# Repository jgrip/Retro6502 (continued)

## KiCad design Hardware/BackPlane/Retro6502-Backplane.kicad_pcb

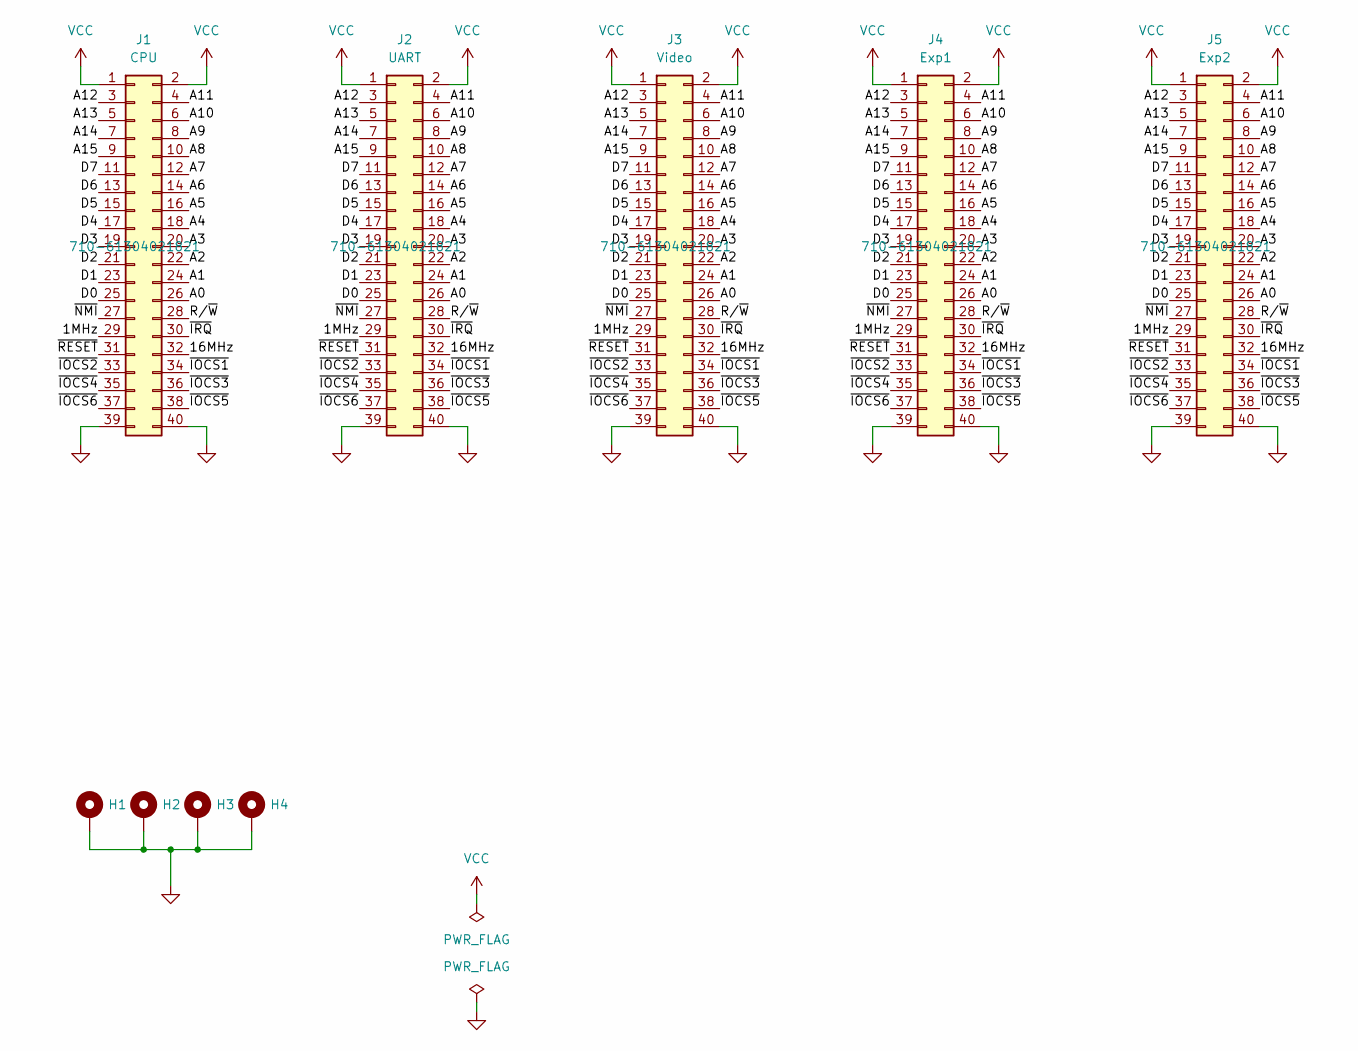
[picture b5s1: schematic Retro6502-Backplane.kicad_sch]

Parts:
H1, H2, H3, H4: MountingHole_Pad; MountingHole_3.2mm_M3_Pad_Via
J1: CPU; PinSocket_2x20_P2.54mm_Vertical; Mouser 710-61304021821
J2: UART; PinSocket_2x20_P2.54mm_Vertical; Mouser 710-61304021821
J3: Video; PinSocket_2x20_P2.54mm_Vertical; Mouser 710-61304021821
J4: Exp1; PinSocket_2x20_P2.54mm_Vertical; Mouser 710-61304021821
J5: Exp2; PinSocket_2x20_P2.54mm_Vertical; Mouser 710-61304021821

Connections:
/1MHz: J1.29, J2.29, J3.29, J4.29, J5.29
/16MHz: J1.32, J2.32, J3.32, J4.32, J5.32
/A0: J1.26, J2.26, J3.26, J4.26, J5.26
/A1: J1.24, J2.24, J3.24, J4.24, J5.24
/A2: J1.22, J2.22, J3.22, J4.22, J5.22
/A3: J1.20, J2.20, J3.20, J4.20, J5.20
/A4: J1.18, J2.18, J3.18, J4.18, J5.18
/A5: J1.16, J2.16, J3.16, J4.16, J5.16
/A6: J1.14, J2.14, J3.14, J4.14, J5.14
/A7: J1.12, J2.12, J3.12, J4.12, J5.12
/A8: J1.10, J2.10, J3.10, J4.10, J5.10
/A9: J1.8, J2.8, J3.8, J4.8, J5.8
/A10: J1.6, J2.6, J3.6, J4.6, J5.6
/A11: J1.4, J2.4, J3.4, J4.4, J5.4
/A12: J1.3, J2.3, J3.3, J4.3, J5.3
/A13: J1.5, J2.5, J3.5, J4.5, J5.5
/A14: J1.7, J2.7, J3.7, J4.7, J5.7
/A15: J1.9, J2.9, J3.9, J4.9, J5.9
/D0: J1.25, J2.25, J3.25, J4.25, J5.25
/D1: J1.23, J2.23, J3.23, J4.23, J5.23
/D2: J1.21, J2.21, J3.21, J4.21, J5.21
/D3: J1.19, J2.19, J3.19, J4.19, J5.19
/D4: J1.17, J2.17, J3.17, J4.17, J5.17
/D5: J1.15, J2.15, J3.15, J4.15, J5.15
/D6: J1.13, J2.13, J3.13, J4.13, J5.13
/D7: J1.11, J2.11, J3.11, J4.11, J5.11
/R/~W: J1.28, J2.28, J3.28, J4.28, J5.28
/~IOCS1: J1.34, J2.34, J3.34, J4.34, J5.34
/~IOCS2: J1.33, J2.33, J3.33, J4.33, J5.33
/~IOCS3: J1.36, J2.36, J3.36, J4.36, J5.36
/~IOCS4: J1.35, J2.35, J3.35, J4.35, J5.35
/~IOCS5: J1.38, J2.38, J3.38, J4.38, J5.38
/~IOCS6: J1.37, J2.37, J3.37, J4.37, J5.37
/~IRQ: J1.30, J2.30, J3.30, J4.30, J5.30
/~NMI: J1.27, J2.27, J3.27, J4.27, J5.27
/~RESET: J1.31, J2.31, J3.31, J4.31, J5.31
GND: H1.1, H2.1, H3.1, H4.1, J1.39, J1.40, J2.39, J2.40, J3.39, J3.40, J4.39, J4.40, J5.39, J5.40
VCC: J1.1, J1.2, J2.1, J2.2, J3.1, J3.2, J4.1, J4.2, J5.1, J5.2

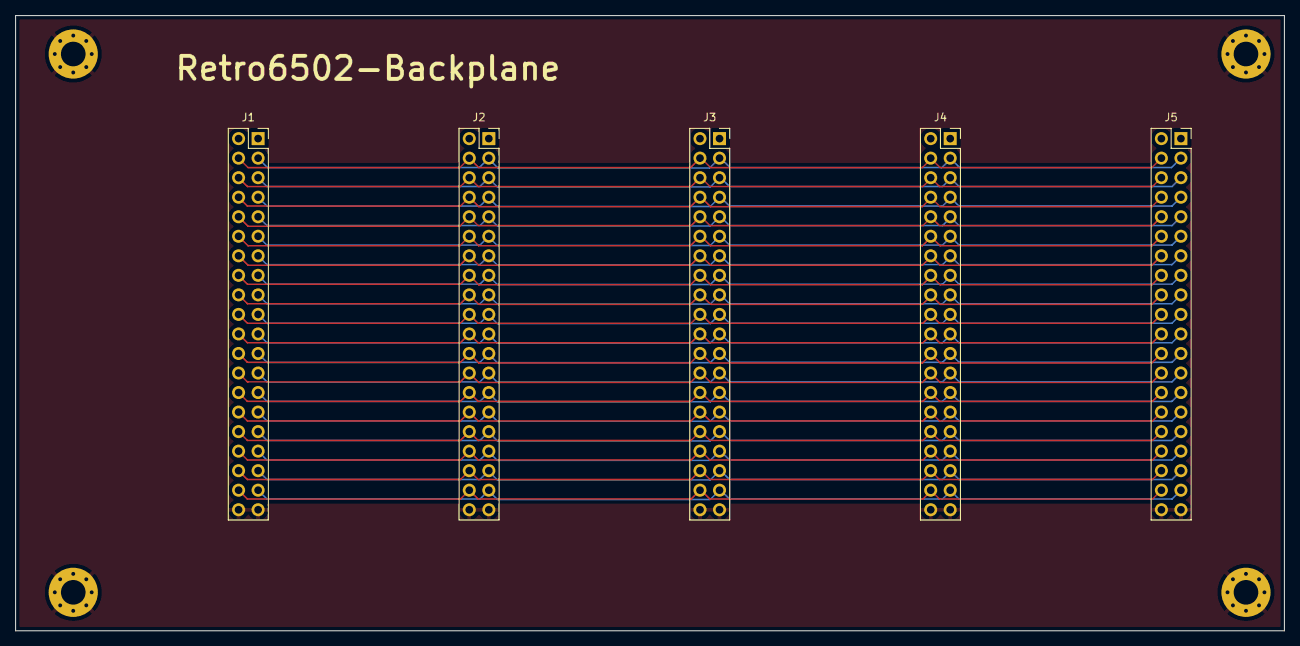
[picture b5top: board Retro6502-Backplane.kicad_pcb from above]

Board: 2 copper layers, 165.0 x 80.0 mm, 9 parts (0 on the bottom side), 38 nets.

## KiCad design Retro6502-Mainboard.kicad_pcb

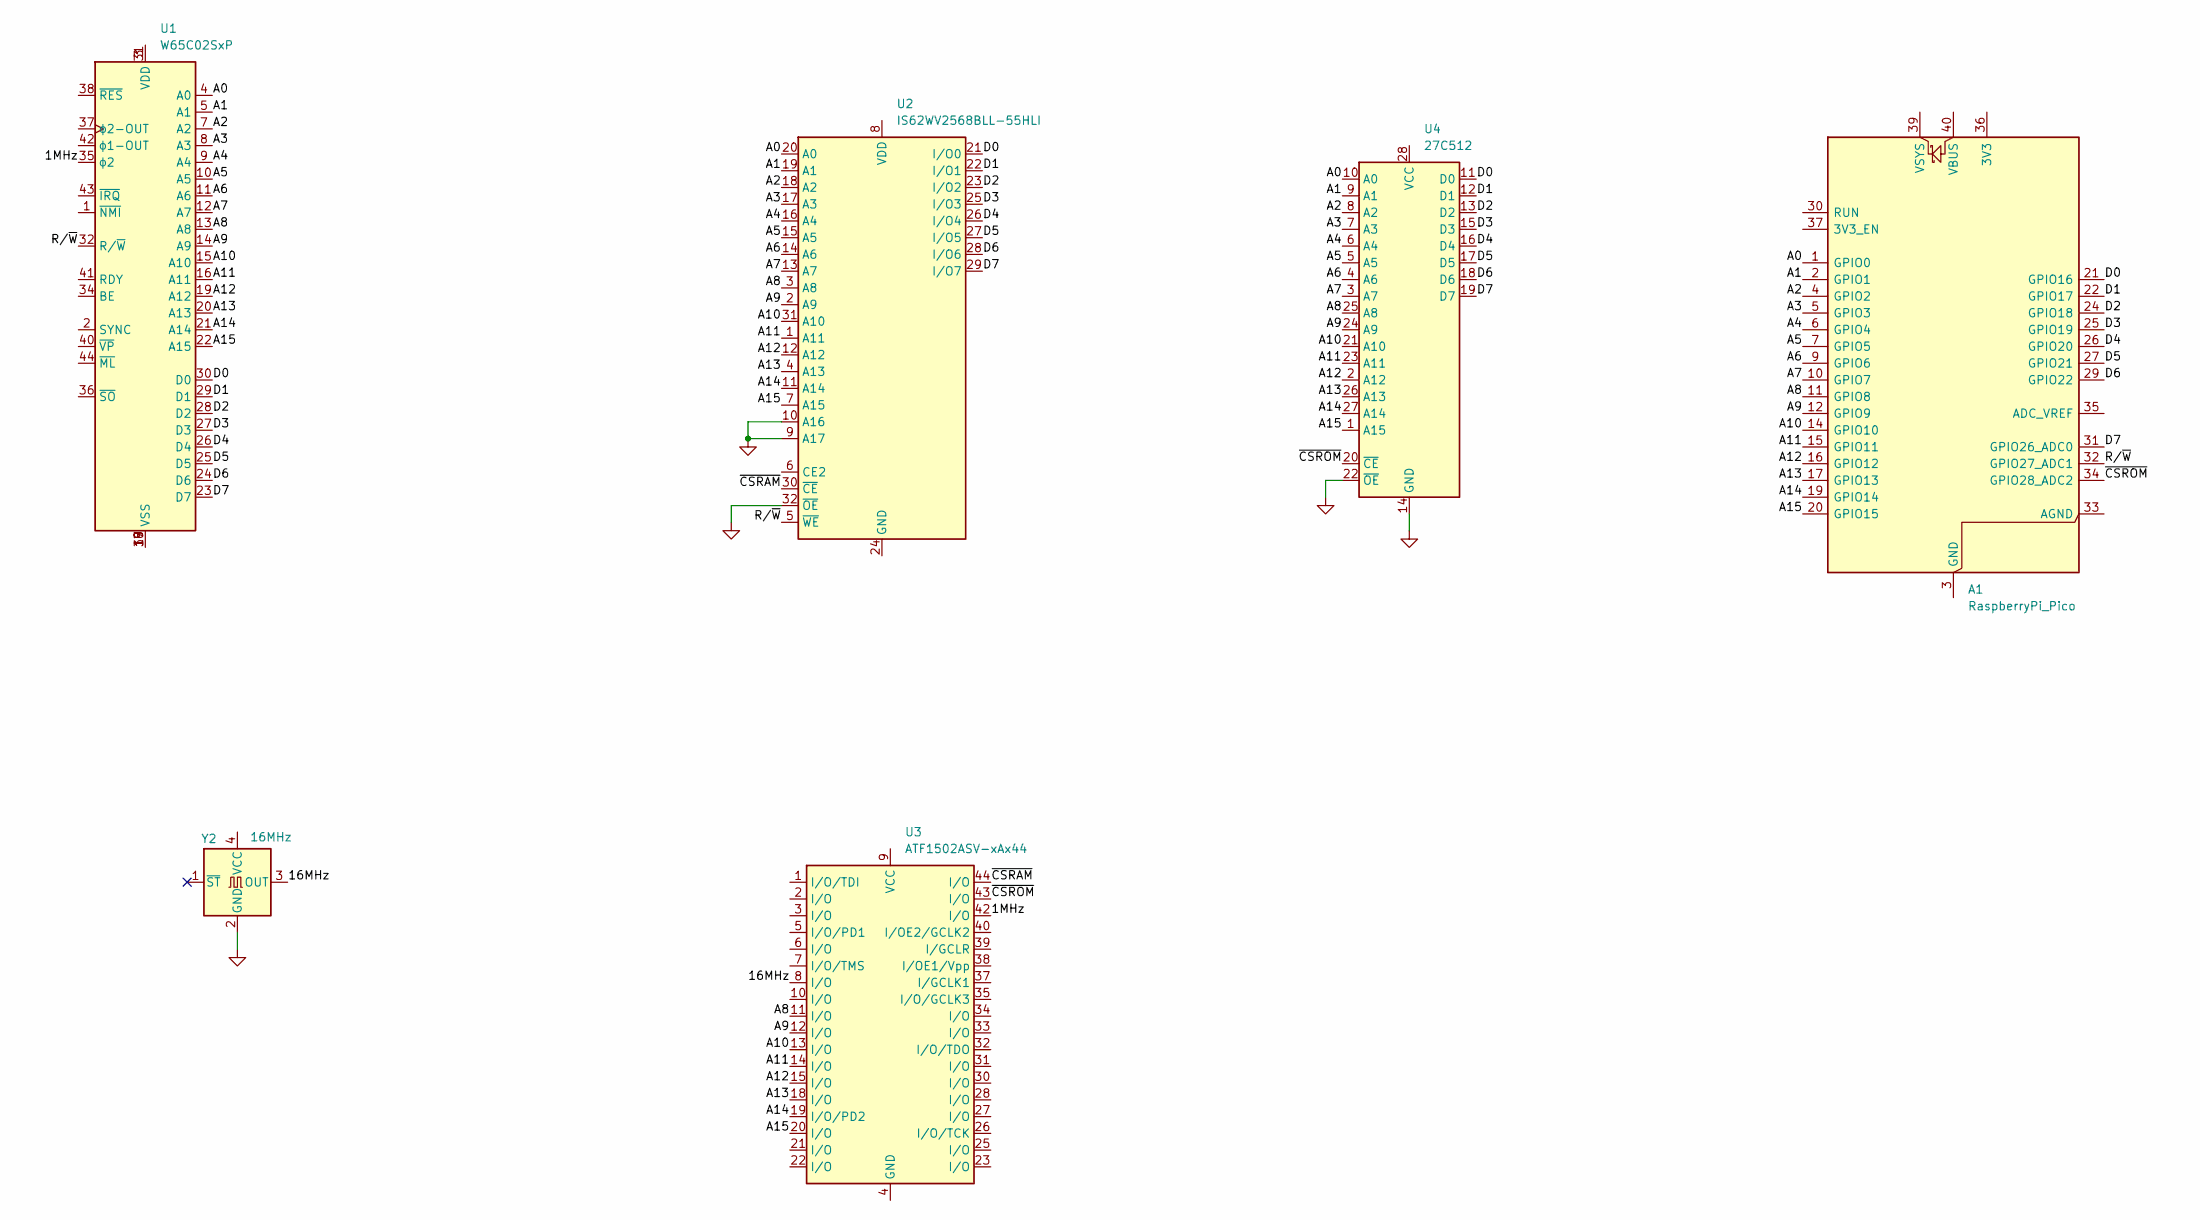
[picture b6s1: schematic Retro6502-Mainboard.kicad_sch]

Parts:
A1: RaspberryPi_Pico; RaspberryPi_Pico_Common_Unspecified
U1: W65C02SxP; TQFP-44_10x10mm_P0.8mm; Mouser 955-W65C02S6TQG-14
U2: IS62WV2568BLL-55HLI; TSOP-I-32_11.8x8mm_P0.5mm
U3: ATF1502ASV-xAx44; TQFP-44_10x10mm_P0.8mm
U4: 27C512; DIP-28_W15.24mm
Y2: 16MHz; Oscillator_SMD_SeikoEpson_SG8002CA-4Pin_7.0x5.0mm

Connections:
/1MHz: U1.35 (ϕ2), U3.42 (I/O)
/16MHz: U3.8 (I/O), Y2.3 (OUT)
/A0: A1.1 (GPIO0), U1.4 (A0), U2.20 (A0), U4.10 (A0)
/A1: A1.2 (GPIO1), U1.5 (A1), U2.19 (A1), U4.9 (A1)
/A2: A1.4 (GPIO2), U1.7 (A2), U2.18 (A2), U4.8 (A2)
/A3: A1.5 (GPIO3), U1.8 (A3), U2.17 (A3), U4.7 (A3)
/A4: A1.6 (GPIO4), U1.9 (A4), U2.16 (A4), U4.6 (A4)
/A5: A1.7 (GPIO5), U1.10 (A5), U2.15 (A5), U4.5 (A5)
/A6: A1.9 (GPIO6), U1.11 (A6), U2.14 (A6), U4.4 (A6)
/A7: A1.10 (GPIO7), U1.12 (A7), U2.13 (A7), U4.3 (A7)
/A8: A1.11 (GPIO8), U1.13 (A8), U2.3 (A8), U3.11 (I/O), U4.25 (A8)
/A9: A1.12 (GPIO9), U1.14 (A9), U2.2 (A9), U3.12 (I/O), U4.24 (A9)
/A10: A1.14 (GPIO10), U1.15 (A10), U2.31 (A10), U3.13 (I/O), U4.21 (A10)
/A11: A1.15 (GPIO11), U1.16 (A11), U2.1 (A11), U3.14 (I/O), U4.23 (A11)
/A12: A1.16 (GPIO12), U1.19 (A12), U2.12 (A12), U3.15 (I/O), U4.2 (A12)
/A13: A1.17 (GPIO13), U1.20 (A13), U2.4 (A13), U3.18 (I/O), U4.26 (A13)
/A14: A1.19 (GPIO14), U1.21 (A14), U2.11 (A14), U3.19 (I/O/PD2), U4.27 (A14)
/A15: A1.20 (GPIO15), U1.22 (A15), U2.7 (A15), U3.20 (I/O), U4.1 (A15)
/D0: A1.21 (GPIO16), U1.30 (D0), U2.21 (I/O0), U4.11 (D0)
/D1: A1.22 (GPIO17), U1.29 (D1), U2.22 (I/O1), U4.12 (D1)
/D2: A1.24 (GPIO18), U1.28 (D2), U2.23 (I/O2), U4.13 (D2)
/D3: A1.25 (GPIO19), U1.27 (D3), U2.25 (I/O3), U4.15 (D3)
/D4: A1.26 (GPIO20), U1.26 (D4), U2.26 (I/O4), U4.16 (D4)
/D5: A1.27 (GPIO21), U1.25 (D5), U2.27 (I/O5), U4.17 (D5)
/D6: A1.29 (GPIO22), U1.24 (D6), U2.28 (I/O6), U4.18 (D6)
/D7: A1.31 (GPIO26_ADC0), U1.23 (D7), U2.29 (I/O7), U4.19 (D7)
/R/~W: A1.32 (GPIO27_ADC1), U1.32 (R/~W), U2.5 (~WE)
/~CSRAM: U2.30 (~CE), U3.44 (I/O)
/~CSROM: A1.34 (GPIO28_ADC2), U3.43 (I/O), U4.20 (~CE)
GND: U2.9 (A17), U2.10 (A16), U2.32 (~OE), U4.14 (GND), U4.22 (~OE), Y2.2 (GND)
unnamed: A1.3 (GND), A1.8 (GND), A1.13 (GND), A1.18 (GND), A1.23 (GND), A1.28 (GND), A1.38 (GND)
unnamed: U1.3 (VDD), U1.31 (VDD)
unnamed: U1.17 (VSS), U1.18 (VSS), U1.39 (VSS)
unnamed: U3.4 (GND), U3.16 (GND), U3.24 (GND), U3.36 (GND)
unnamed: U3.9 (VCC), U3.17 (VCC), U3.29 (VCC), U3.41 (VCC)

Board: 2 copper layers, 6 parts (0 on the bottom side), 35 nets, no tracks yet.

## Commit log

2025-04-23 Initial revision
2025-05-05 Finished all four board, restructured repo
2025-05-06 Memory space layout
2025-05-06 Add PLA logic equations
2025-05-06 Initial FW work
2025-05-17 Add VIA card
2025-05-17 Add license
2025-05-17 Migrated away
